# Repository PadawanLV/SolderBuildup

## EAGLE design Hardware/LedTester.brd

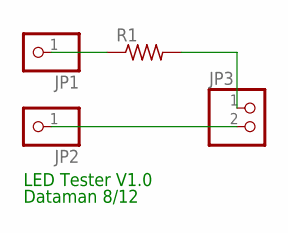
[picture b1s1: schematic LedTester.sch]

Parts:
JP1, JP2: PINHD-1X1; 1X01
JP3: PINHD-1X2; 1X02
R1: R-US_0207/10; 0207/10

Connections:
unnamed: JP1.1, R1.1
unnamed: JP3.1, R1.2
unnamed: JP2.1, JP3.2

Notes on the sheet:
LED Tester V1.0
Dataman 8/12

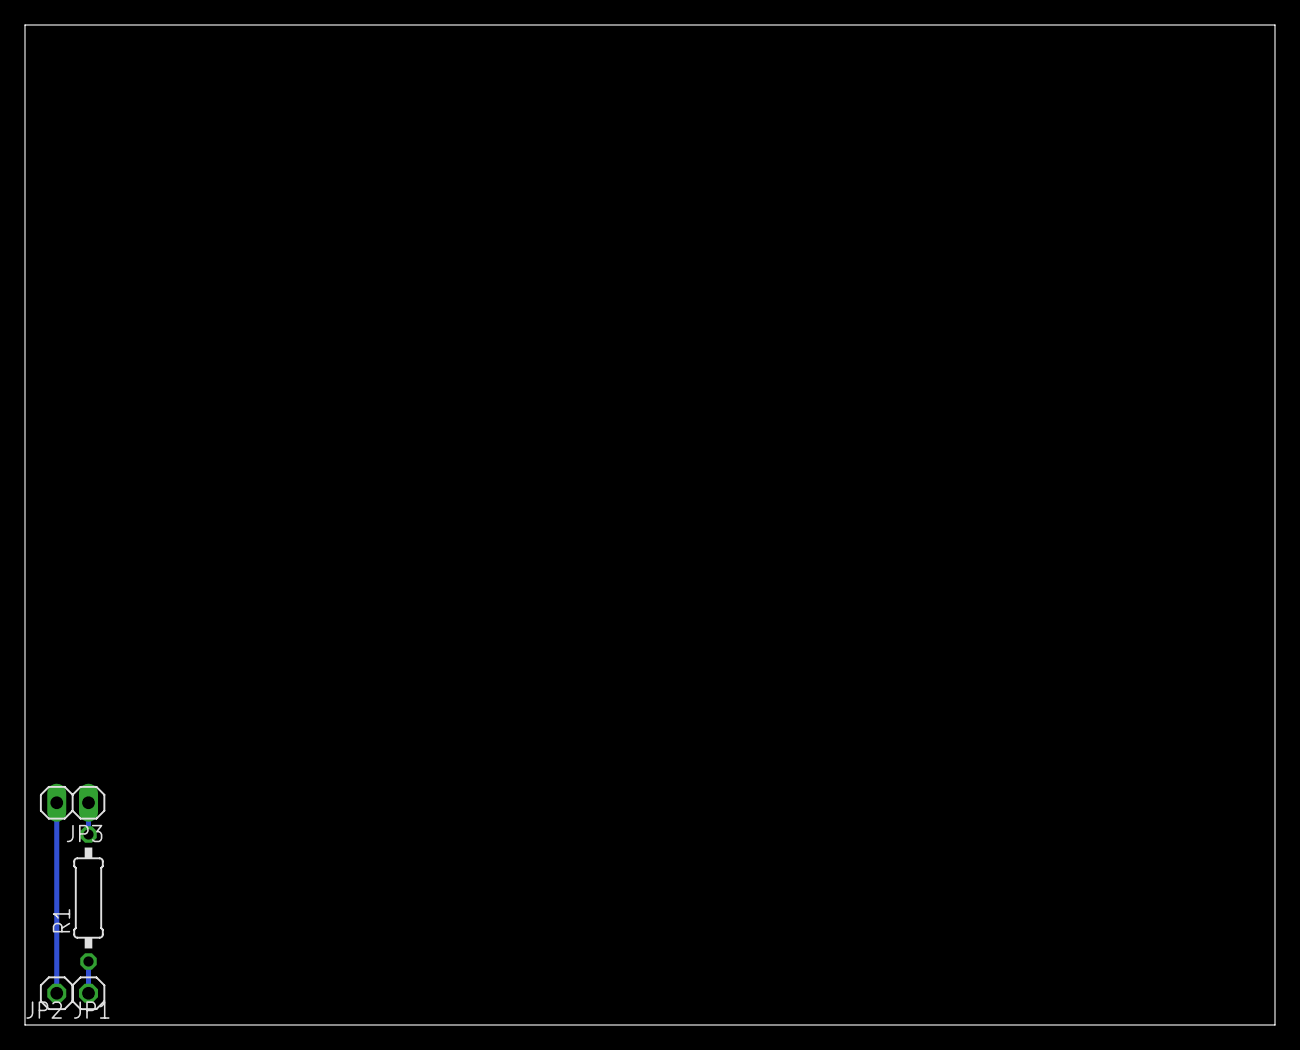
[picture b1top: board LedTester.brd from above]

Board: 2 copper layers, 100.0 x 80.0 mm, 4 parts (0 on the bottom side), 3 nets.

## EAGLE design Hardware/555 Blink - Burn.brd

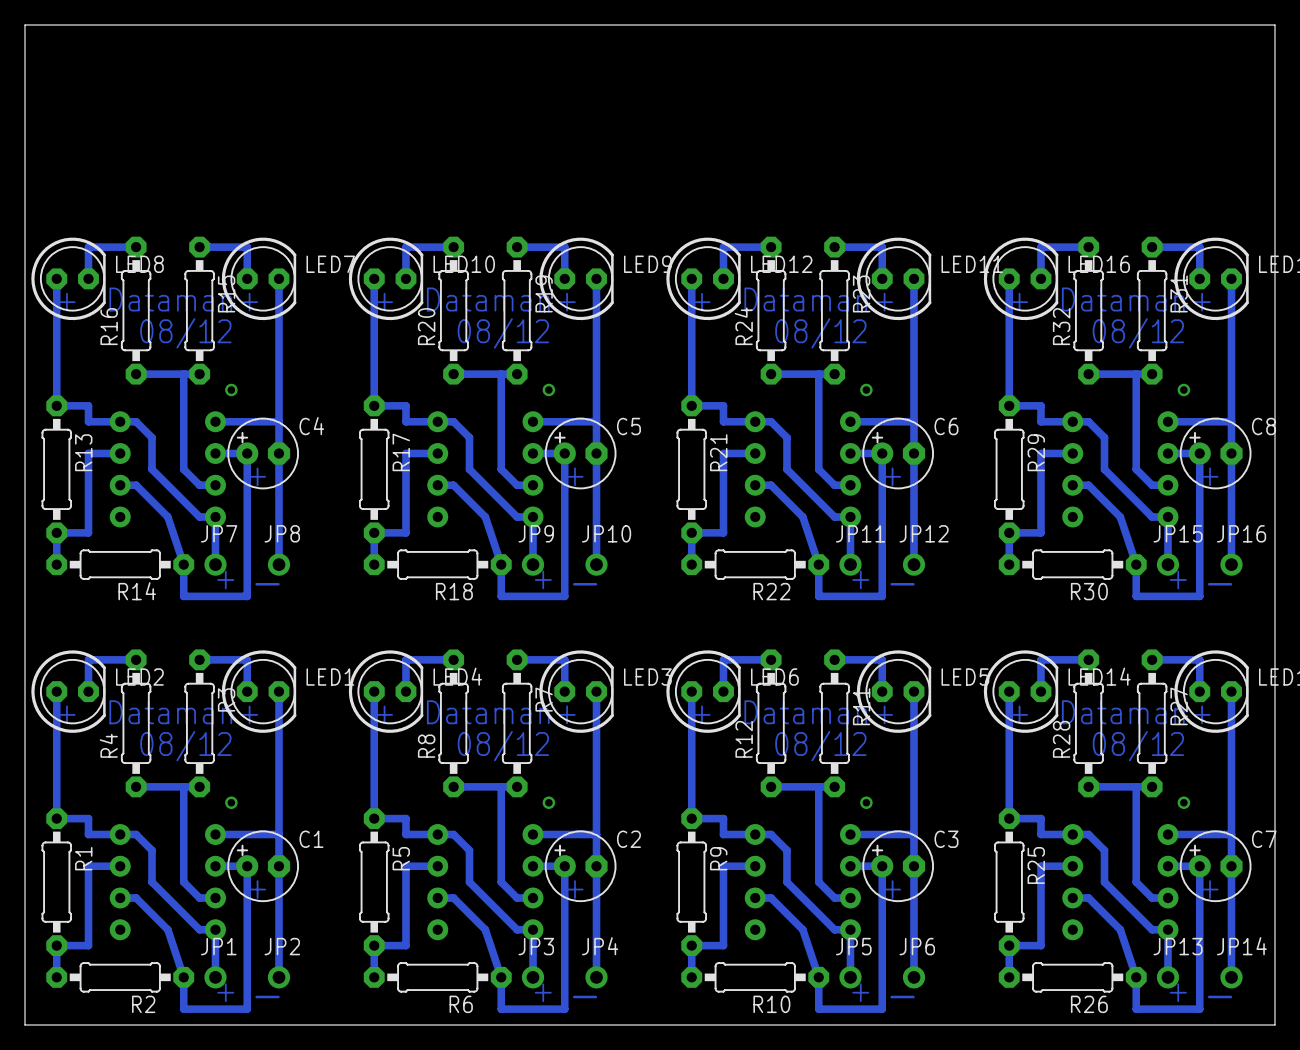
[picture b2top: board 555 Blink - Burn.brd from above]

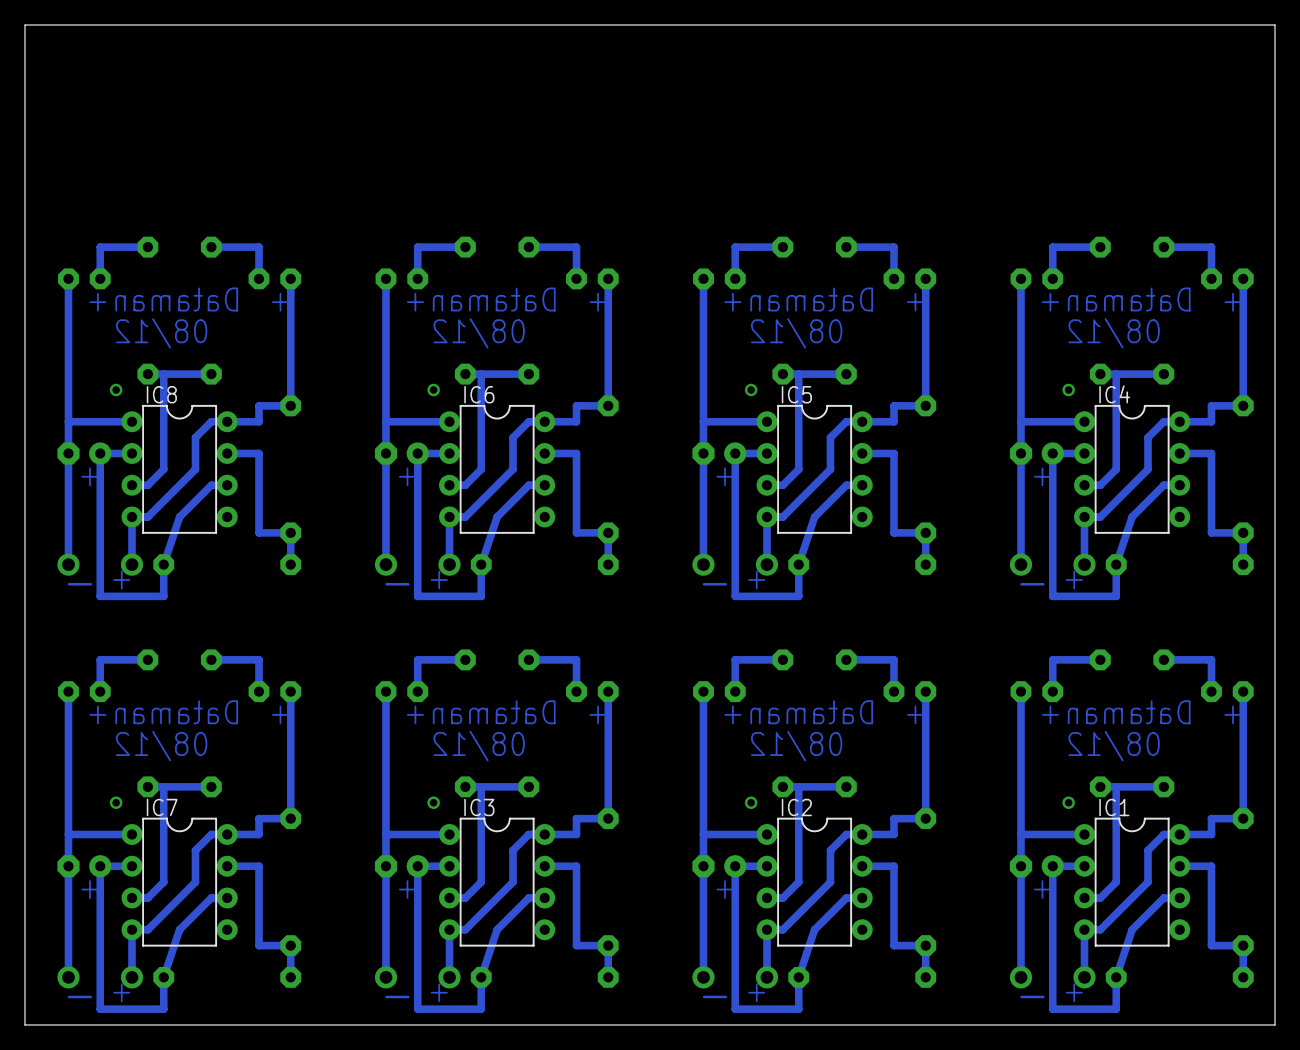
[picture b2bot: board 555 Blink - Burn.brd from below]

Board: 2 copper layers, 100.0 x 80.0 mm, 80 parts (8 on the bottom side), 56 nets.

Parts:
C1, C2, C3, C4, C5, C6, C7, C8: E2,5-6
IC1, IC2, IC3, IC4, IC5, IC6, IC7, IC8: LM555N; DIL08-ROUND
JP1, JP2, JP3, JP4, JP5, JP6, JP7, JP8, JP9, JP10, JP11, JP12, JP13, JP14, JP15, JP16: 1X01-CLEANBIG
LED1, LED2, LED3, LED4, LED5, LED6, LED7, LED8, LED9, LED10, LED11, LED12, LED13, LED14, LED15, LED16: LED5MM
R1, R2, R5, R6, R9, R10, R13, R14, R17, R18, R21, R22, R25, R26, R29, R30: 100K; 0207/10
R3, R4, R7, R8, R11, R12, R15, R16, R19, R20, R23, R24, R27, R28, R31, R32: 470; 0207/10

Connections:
+9V: IC1.4, IC1.8, JP1.1, LED2.A, R1.1
+9V1: IC2.4, IC2.8, JP3.1, LED4.A, R5.1
+9V2: IC3.4, IC3.8, JP5.1, LED6.A, R9.1
+9V3: IC4.4, IC4.8, JP7.1, LED8.A, R13.1
+9V4: IC5.4, IC5.8, JP9.1, LED10.A, R17.1
+9V5: IC6.4, IC6.8, JP11.1, LED12.A, R21.1
+9V6: IC7.4, IC7.8, JP13.1, LED14.A, R25.1
+9V7: IC8.4, IC8.8, JP15.1, LED16.A, R29.1
GND: C1.-, IC1.1, JP2.1, LED1.K
GND1: C2.-, IC2.1, JP4.1, LED3.K
GND2: C3.-, IC3.1, JP6.1, LED5.K
GND3: C4.-, IC4.1, JP8.1, LED7.K
GND4: C5.-, IC5.1, JP10.1, LED9.K
GND5: C6.-, IC6.1, JP12.1, LED11.K
GND6: C7.-, IC7.1, JP14.1, LED13.K
GND7: C8.-, IC8.1, JP16.1, LED15.K
unnamed: IC1.3, R3.2, R4.1
unnamed: C1.+, IC1.2, IC1.6, R2.1
unnamed: IC1.7, R1.2, R2.2
unnamed: LED2.K, R4.2
unnamed: IC2.7, R5.2, R6.2
unnamed: LED1.A, R3.1
unnamed: IC2.3, R7.2, R8.1
unnamed: LED3.A, R7.1
unnamed: LED4.K, R8.2
unnamed: C2.+, IC2.2, IC2.6, R6.1
unnamed: IC3.7, R9.2, R10.2
unnamed: IC3.3, R11.2, R12.1
unnamed: LED5.A, R11.1
unnamed: LED6.K, R12.2
unnamed: C3.+, IC3.2, IC3.6, R10.1
unnamed: IC4.7, R13.2, R14.2
unnamed: IC4.3, R15.2, R16.1
unnamed: LED7.A, R15.1
unnamed: LED8.K, R16.2
unnamed: C4.+, IC4.2, IC4.6, R14.1
unnamed: IC5.7, R17.2, R18.2
unnamed: IC5.3, R19.2, R20.1
unnamed: LED9.A, R19.1
unnamed: LED10.K, R20.2
unnamed: C5.+, IC5.2, IC5.6, R18.1
unnamed: IC6.7, R21.2, R22.2
unnamed: IC6.3, R23.2, R24.1
unnamed: LED11.A, R23.1
unnamed: LED12.K, R24.2
unnamed: C6.+, IC6.2, IC6.6, R22.1
unnamed: IC7.7, R25.2, R26.2
unnamed: IC7.3, R27.2, R28.1
unnamed: LED13.A, R27.1
unnamed: LED14.K, R28.2
unnamed: C7.+, IC7.2, IC7.6, R26.1
unnamed: IC8.7, R29.2, R30.2
unnamed: IC8.3, R31.2, R32.1
unnamed: LED15.A, R31.1
unnamed: LED16.K, R32.2
unnamed: C8.+, IC8.2, IC8.6, R30.1

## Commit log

2012-08-23 Initial Version
2012-08-24 Test
2012-08-28 Fixup
    Flip Positive LED
    Connect 2 to 6
2012-08-28 Burn board for mods
2012-09-04 Add presentation and build instructions
2012-09-04 Touchups
2012-09-04 minor touchups
2012-09-04 Er refreshed?
2012-09-04 Final Commit before class
2012-09-04 Ignore eaglecad temp files
2012-09-05 After course cleanup.
    Thank to you all, especially Ryan and Claire, for helping clean up this
    presentation. All comments helpful!
2012-11-27 uncomitted changes from mac
2012-11-28 Class notes from 11/27/2012
